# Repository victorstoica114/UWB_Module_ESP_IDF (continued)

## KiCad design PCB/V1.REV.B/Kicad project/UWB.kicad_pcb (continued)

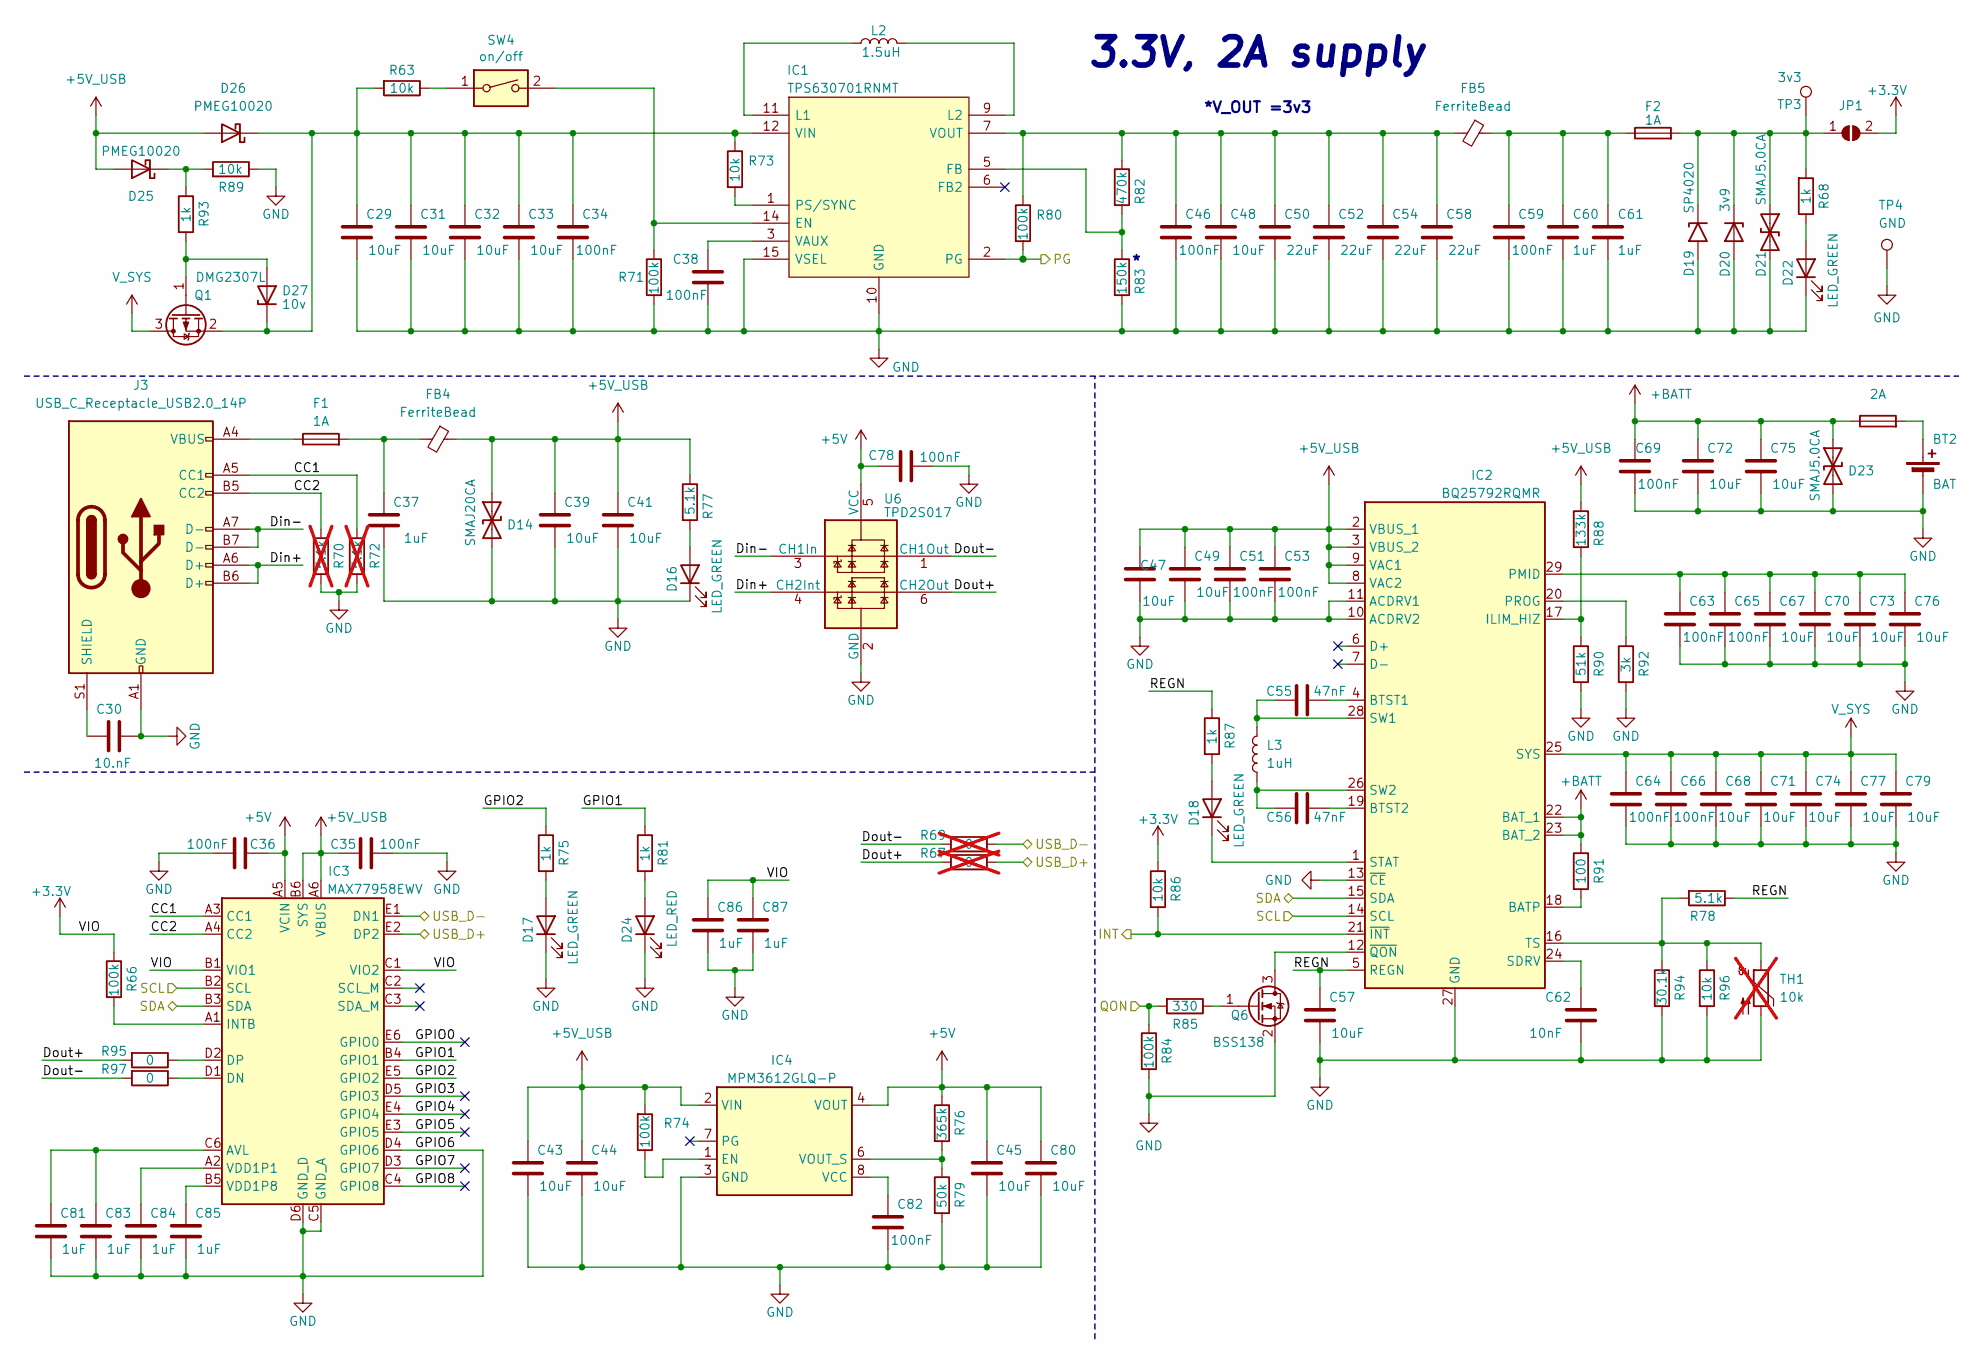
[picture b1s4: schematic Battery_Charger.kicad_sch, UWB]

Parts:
BT2: BAT; JST_PH_B2B-PH-K_1x02_P2.00mm_Vertical; Mfr. part number L475085; JLCPCB Part C131337
C29, C31, C32, C33, C39, C41, C43, C44, C45, C47, C48, C49, C57, C67, C68, C70, C71, C72, C73, C74, C75, C76, C77, C79, C80: 10uF; C_0603_1608Metric; Mfr. part number GRM188Z71A106KA73D; JLCPCB Part C19702
C30: 10.nF; C_1812_4532Metric; Mfr. part number CAS18C471JAGFC; JLCPCB Part C3287694
C34, C35, C36, C38, C46, C51, C53, C59, C63, C64, C65, C66, C69, C78, C82: 100nF; C_0603_1608Metric; Mfr. part number 06035C104KAZ4A; JLCPCB Part C14663
C37, C60, C61, C81, C83, C84, C85, C86, C87: 1uF; C_0603_1608Metric; Mfr. part number 885012206052; JLCPCB Part C15849
C50, C52, C54, C58: 22uF; C_1206_3216Metric; Mfr. part number CL31B226KPHNNNE; JLCPCB Part C12891
C55, C56: 47nF; C_0603_1608Metric; Mfr. part number 885012205054; JLCPCB Part C1622
C62: 10nF; C_0603_1608Metric; Mfr. part number SH18B103K160CT; JLCPCB Part C57112
D14: SMAJ20CA; D_SMA; Mfr. part number SMAJ20CA; JLCPCB Part C134970
D16, D17, D18, D22: LED_GREEN; LED_0603_1608Metric; Mfr. part number 150060VS75000; JLCPCB Part C22371297
D19: SP4020; D_SOD-323; Mfr. part number SP4020-01FTG-C; JLCPCB Part C126842
D20: 3v9; D_SMA; Mfr. part number BZG05C3V9-M3-08
D21, D23: SMAJ5.0CA; D_SMA; Mfr. part number SMAJ5.0CA; JLCPCB Part C83324
D24: LED_RED; LED_0603_1608Metric; Mfr. part number 150060RS75000; JLCPCB Part C965799
D25, D26: PMEG10020; D_SOD-123F; Mfr. part number PMEG10020ELR-QX; JLCPCB Part C8597
D27: 10v; D_SOD-123F; Mfr. part number 78-MMSZ4697-HE3_A-08; JLCPCB Part C2922775
F1, F2: 1A; Fuse_1206_3216Metric; Mfr. part number C1T 1; JLCPCB Part C2838907
F3: 2A; Fuse_1206_3216Metric; Mfr. part number C1T 2; JLCPCB Part C18211642
FB4, FB5: FerriteBead; L_0805_2012Metric; Mfr. part number BLM21SP601SN1D; JLCPCB Part C3716677
IC1: TPS630701RNMT; TPS630702RNMT; Mfr. part number TPS630702RNMR; JLCPCB Part C181473
IC2: BQ25792RQMR; Mfr. part number BQ25792RQMR; JLCPCB Part C2862876
IC3: MAX77958EWV; BGA30C50P6X5_307X262X69; Manufacturer_Part_Number MAX77958EWV
IC4: MPM3612GLQ-P; MPM3612GLQ33P; Mfr. part number MPM3612GLQ-P
J3: USB_C_Receptacle_USB2.0_14P; USB_C_Receptacle_GCT_USB4105-xx-A_16P_TopMnt_Horizontal; Mfr. part number USB4105-GF-A-120; JLCPCB Part C5184243
JP1: SolderJumper_2_Open; SolderJumper-2_P1.3mm_Open_RoundedPad1.0x1.5mm
L2: 1.5uH; L_Taiyo-Yuden_NR-60xx; Mfr. part number NRM6045T1R5NMRRV; JLCPCB Part C3221450
L3: 1uH; L_Taiyo-Yuden_NR-60xx; Mfr. part number NRS6045T1R0NMGKV; JLCPCB Part C1331878
Q1: DMG2307L; SOT-23; Mfr. part number DMG2307L-7; JLCPCB Part C102620
Q6: BSS138; SOT-23; Mfr. part number BSS138; JLCPCB Part C5224261
R63, R73, R86, R89, R96: 10k; R_0603_1608Metric; Mfr. part number CR0603-FX-1002ELF; JLCPCB Part C25804
R66, R71, R74, R80, R84: 100k; R_0603_1608Metric; Mfr. part number RC0603FR-10100KL; JLCPCB Part C25803
R67, R69: 0; R_0603_1608Metric; Mfr. part number RC0603FR-130RL; JLCPCB Part C21189; not fitted
R68, R75, R81, R87, R93: 1k; R_0603_1608Metric; Mfr. part number AC0603DR-071KL; JLCPCB Part C21190
R70, R72: 5.1k; R_0603_1608Metric; Mfr. part number AC0603FR-135K1L; JLCPCB Part C23186; not fitted
R76: 365k; R_0603_1608Metric; Mfr. part number RC0603FR-07365KL; JLCPCB Part C23031
R77, R78: 5.1k; R_0603_1608Metric; Mfr. part number AC0603FR-135K1L; JLCPCB Part C23186
R79: 50k; R_0603_1608Metric; Mfr. part number AC0603FR-0751KL; JLCPCB Part C861451
R82: 470k; R_0603_1608Metric; Mfr. part number AC0603FR-07470KL; JLCPCB Part C23178
R83: 150k; R_0603_1608Metric; Mfr. part number RC0603FR-13150KL; JLCPCB Part C22807
R85: 330; R_0603_1608Metric; Mfr. part number RE0603FRE07330RL; JLCPCB Part C23138
R88: 133k; R_0603_1608Metric; Mfr. part number RC0603FR-07133KL; JLCPCB Part C22870
R90: 51k; R_0603_1608Metric; Mfr. part number AC0603FR-0751KL; JLCPCB Part C18672
R91: 100; R_0603_1608Metric; Mfr. part number RE0603FRE07330RL; JLCPCB Part C22775
R92: 3k; R_0603_1608Metric; Mfr. part number 603-RC0603JR-073KL
R94: 30.1k; R_0603_1608Metric; Mfr. part number RC0603FR-0730K1L; JLCPCB Part C23000
R95, R97: 0; R_0603_1608Metric; Mfr. part number RC0603FR-130RL; JLCPCB Part C21189
SW4: on/off; SW_SPDT_PCM12; Mfr. part number PCM12SMTBR; JLCPCB Part C18197923
TH1: 10k; JST_PH_B2B-PH-K_1x02_P2.00mm_Vertical; Mfr. Part No. B2B-PH-K-S (LF)(SN); JLCPCB Part C25804; not fitted
TP3: 3v3; TestPoint_Pad_D2.0mm
TP4: GND; TestPoint_Pad_D2.0mm
U6: TPD2S017; SOT-23-6; Mfr. part number TPD2S017DBVR; JLCPCB Part C880115

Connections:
+3.3V: C86.1, C87.1, IC3.B1 (VIO1), IC3.C1 (VIO2), JP1.2 (B), R66.1, R86.1; also elsewhere on the board
+5V: C36.1, C45.1, C78.1, C80.1, IC3.A5 (VCIN), IC4.4 (VOUT), IC4.5 (VOUT_2), R76.1, U6.5 (VCC)
+5V_USB: C35.1, C39.1, C41.1, C43.1, C44.1, C47.1, C49.1, C51.1, C53.1, D14.1 (A1), D25.2 (A), D26.2 (A), FB4.1, IC2.2 (VBUS_1), IC2.3 (VBUS_2), IC2.8 (VAC2), IC2.9 (VAC1), IC2.31 (VAC1_2), IC3.A6 (VBUS), IC3.B6 (SYS), IC4.2 (VIN), R74.2, R77.1, R88.1
+BATT: C69.1, C72.1, C75.1, D23.1 (A1), F3.1, IC2.22 (BAT_1), IC2.23 (BAT_2), R91.1
/Battery_Charger and Power_Supply/CC1: IC3.A3 (CC1), J3.A5 (CC1), R72.1
/Battery_Charger and Power_Supply/CC2: IC3.A4 (CC2), J3.B5 (CC2), R70.1
/Battery_Charger and Power_Supply/Din+: J3.A6 (D+), J3.B6 (D+), U6.4 (CH2Int)
/Battery_Charger and Power_Supply/Din-: J3.A7 (D-), J3.B7 (D-), U6.3 (CH1In)
/Battery_Charger and Power_Supply/Dout+: R67.2, R95.2, U6.6 (CH2Out)
/Battery_Charger and Power_Supply/Dout-: R69.2, R97.2, U6.1 (CH1Out)
/Battery_Charger and Power_Supply/GPIO0: IC3.E6 (GPIO0)
/Battery_Charger and Power_Supply/GPIO1: IC3.B4 (GPIO1), R81.1
/Battery_Charger and Power_Supply/GPIO2: IC3.E5 (GPIO2), R75.1
/Battery_Charger and Power_Supply/GPIO3: IC3.D5 (GPIO3)
/Battery_Charger and Power_Supply/GPIO4: IC3.E4 (GPIO4)
/Battery_Charger and Power_Supply/GPIO5: IC3.E3 (GPIO5)
/Battery_Charger and Power_Supply/GPIO7: IC3.D3 (GPIO7)
/Battery_Charger and Power_Supply/GPIO8: IC3.C4 (GPIO8)
/Battery_Charger and Power_Supply/INT: IC2.21 (~INT), R86.2; also elsewhere on the board
/Battery_Charger and Power_Supply/PG: IC1.2 (PG), R80.2; also elsewhere on the board
/Battery_Charger and Power_Supply/QON: R84.1, R85.2; also elsewhere on the board
/Battery_Charger and Power_Supply/REGN: C57.1, IC2.5 (REGN), R78.1, R87.1
/Battery_Charger and Power_Supply/SCL: IC2.14 (SCL), IC3.B2 (SCL); also elsewhere on the board
/Battery_Charger and Power_Supply/SDA: IC2.15 (SDA), IC3.B3 (SDA); also elsewhere on the board
/Battery_Charger and Power_Supply/USB_D+: IC3.E2 (DP2), R67.1; also elsewhere on the board
/Battery_Charger and Power_Supply/USB_D-: IC3.E1 (DN1), R69.1; also elsewhere on the board
GND: BT2.2 (-), C29.2, C30.2, C31.2, C32.2, C33.2, C34.2, C35.2, C36.2, C37.2, C38.2, C39.2, C41.2, C43.2, C44.2, C45.2, C46.2, C47.2, C48.2, C49.2, C50.2, C51.2, C52.2, C53.2, C54.2, C57.2, C58.2, C59.2, C60.2, C61.2, C62.2, C63.2, C64.2, C65.2, C66.2, C67.2, C68.2, C69.2, C70.2, C71.2, C72.2, C73.2, C74.2, C75.2, C76.2, C77.2, C78.2, C79.2, C80.2, C81.2, C82.2, C83.2, C84.2, C85.2, C86.2, C87.2, D14.2 (A2), D16.1 (K), D17.1 (K), D19.2 (A2), D20.2 (A), D21.2 (A2), D22.1 (K), D23.2 (A2), D24.1 (K), IC1.4 (GND), IC1.10 (GND), IC1.15 (VSEL), IC2.10 (ACDRV2), IC2.11 (ACDRV1), IC2.13 (~CE), IC2.27 (GND), IC3.C5 (GND_A), IC3.D4 (GPIO6), IC3.D6 (GND_D), IC4.3 (GND), IC4.9 (GND_2), J3.A1 (GND), J3.A12 (GND), J3.B1 (GND), J3.B12 (GND), Q6.2 (S), R70.2, R71.2, R72.2, R79.2, R83.2, R84.2, R89.1, R90.2, R92.2, R94.2, R96.2, TH1.2, TP4.1, U6.2 (GND); also elsewhere on the board
unnamed: BT2.1 (+), F3.2
unnamed: C37.1, F1.2, FB4.2
unnamed: C59.1, C60.1, C61.1, F2.1, FB5.1
unnamed: D16.2 (A), R77.2
unnamed: D17.2 (A), R75.2
unnamed: D18.2 (A), R87.2
unnamed: D18.1 (K), IC2.1 (STAT), IC2.30 (STAT_2)
unnamed: D19.1 (A1), D20.1 (K), D21.1 (A1), F2.2, JP1.1 (A), R68.2, TP3.1
unnamed: D22.2 (A), R68.1
unnamed: D24.2 (A), R81.2
unnamed: D25.1 (K), R89.2, R93.1
unnamed: C29.1, C31.1, C32.1, C33.1, C34.1, D26.1 (K), D27.1 (K), IC1.12 (VIN), IC1.13 (VIN_2), IC1.A12 (VIN_3), Q1.2 (S), R63.2, R73.1
unnamed: D27.2 (A), Q1.1 (G), R93.2
unnamed: F1.1, J3.A4 (VBUS), J3.A9 (VBUS), J3.B4 (VBUS), J3.B9 (VBUS)
unnamed: IC1.14 (EN), R71.1, SW4.2
unnamed: IC1.5 (FB), R82.2, R83.1
unnamed: IC1.11 (L1), L2.2
unnamed: IC1.9 (L2), L2.1
unnamed: IC1.1 (PS/SYNC), R73.2
unnamed: C38.1, IC1.3 (VAUX)
unnamed: C46.1, C48.1, C50.1, C52.1, C54.1, C58.1, FB5.2, IC1.7 (VOUT), IC1.8 (VOUT_2), IC1.A7 (VOUT_3), R80.1, R82.1
unnamed: IC2.18 (BATP), R91.2
unnamed: C55.2, IC2.4 (BTST1)
unnamed: C56.2, IC2.19 (BTST2)
unnamed: IC2.17 (ILIM_HIZ), R88.2, R90.1
unnamed: C63.1, C65.1, C67.1, C70.1, C73.1, C76.1, IC2.29 (PMID)
unnamed: IC2.20 (PROG), R92.1
unnamed: C62.1, IC2.24 (SDRV), IC2.33 (SDRV_2)
unnamed: C55.1, IC2.28 (SW1), L3.2
unnamed: C56.1, IC2.26 (SW2), L3.1
unnamed: IC2.16 (TS), IC2.32 (TS_2), R78.2, R94.1, R96.1, TH1.1
unnamed: IC2.12 (~QON), Q6.3 (D)
unnamed: C81.1, C83.1, IC3.C6 (AVL)
unnamed: IC3.D1 (DN), R97.1
unnamed: IC3.D2 (DP), R95.1
unnamed: IC3.A1 (INTB), R66.2
unnamed: C84.1, IC3.A2 (VDD1P1)
unnamed: C85.1, IC3.B5 (VDD1P8)
unnamed: IC4.1 (EN), R74.1
unnamed: C82.1, IC4.8 (VCC)
unnamed: IC4.6 (VOUT_S), R76.2, R79.1
unnamed: C30.1, J3.S1 (SHIELD)
unnamed: Q6.1 (G), R85.1
unnamed: R63.1, SW4.1
V_SYS: C64.1, C66.1, C68.1, C71.1, C74.1, C77.1, C79.1, IC2.25 (SYS), Q1.3 (D)

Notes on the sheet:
3.3V, 2A supply
*V_OUT =3v3

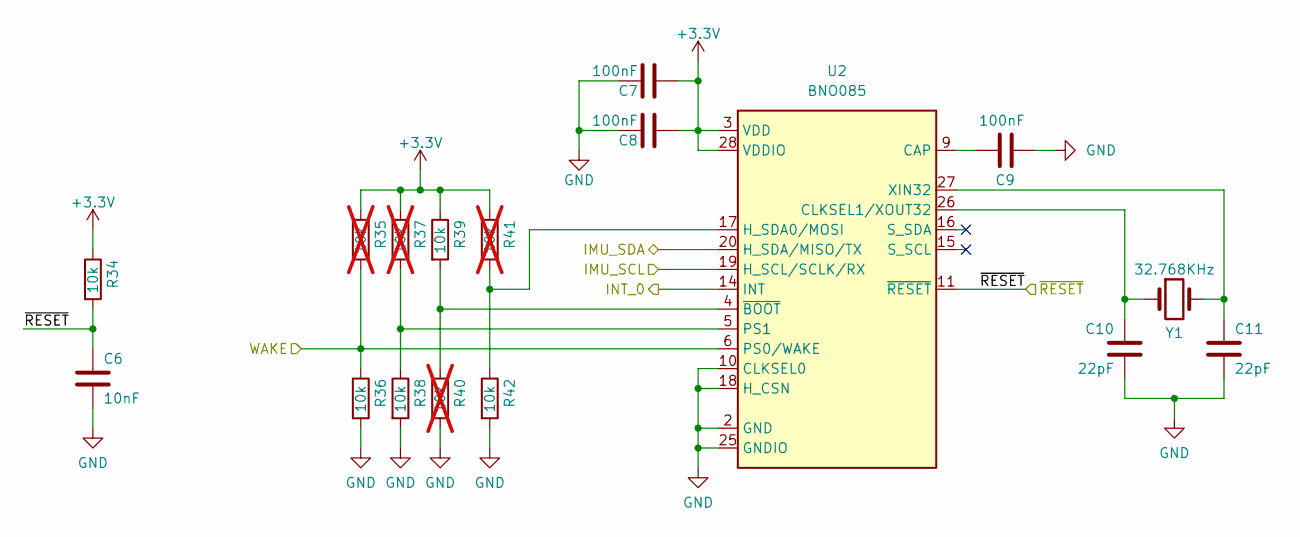
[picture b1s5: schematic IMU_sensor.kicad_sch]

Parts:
C6: 10nF; C_0603_1608Metric; Mfr. part number SH18B103K160CT; JLCPCB Part C57112
C7, C8, C9: 100nF; C_0603_1608Metric; Mfr. part number 06035C104KAZ4A; JLCPCB Part C14663
C10, C11: 22pF; C_0603_1608Metric; Mfr. part number 06033C220KAT2A; JLCPCB Part C1653
R34, R36, R38, R39, R42: 10k; R_0603_1608Metric; Mfr. part number CR0603-FX-1002ELF; JLCPCB Part C25804
R35, R37, R40, R41: 10k; R_0603_1608Metric; Mfr. part number CR0603-FX-1002ELF; JLCPCB Part C25804; not fitted
U2: BNO085; LGA-28_5.2x3.8mm_P0.5mm; Mfr. part number BNO085; JLCPCB Part C5189642
Y1: 32.768KHz; Crystal_SMD_2012-2Pin_2.0x1.2mm; Mfr. part number ABS06-32.768KHZ-T; JLCPCB Part C276423

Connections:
+3.3V: C7.2, C8.2, R34.1, R35.1, R37.1, R39.1, R41.1, U2.3 (VDD), U2.28 (VDDIO); also elsewhere on the board
/Battery_Charger and Power_Supply/SCL: U2.19 (H_SCL/SCLK/RX); also elsewhere on the board
/Battery_Charger and Power_Supply/SDA: U2.20 (H_SDA/MISO/TX); also elsewhere on the board
/ESP32/ESP32_IO14: R35.2, R36.1, U2.6 (PS0/WAKE); also elsewhere on the board
/ESP32/ESP32_IO15: U2.14 (INT); also elsewhere on the board
/IMU_sensor/~RESET: C6.1, R34.2, U2.11 (~RESET); also elsewhere on the board
GND: C6.2, C7.1, C8.1, C9.2, C10.2, C11.2, R36.2, R38.2, R40.2, R42.2, U2.2 (GND), U2.10 (CLKSEL0), U2.18 (H_CSN), U2.25 (GNDIO); also elsewhere on the board
unnamed: C9.1, U2.9 (CAP)
unnamed: C10.1, U2.26 (CLKSEL1/XOUT32), Y1.1
unnamed: R41.2, R42.1, U2.17 (H_SDA0/MOSI)
unnamed: R37.2, R38.1, U2.5 (PS1)
unnamed: C11.1, U2.27 (XIN32), Y1.2
unnamed: R39.2, R40.1, U2.4 (~BOOT)

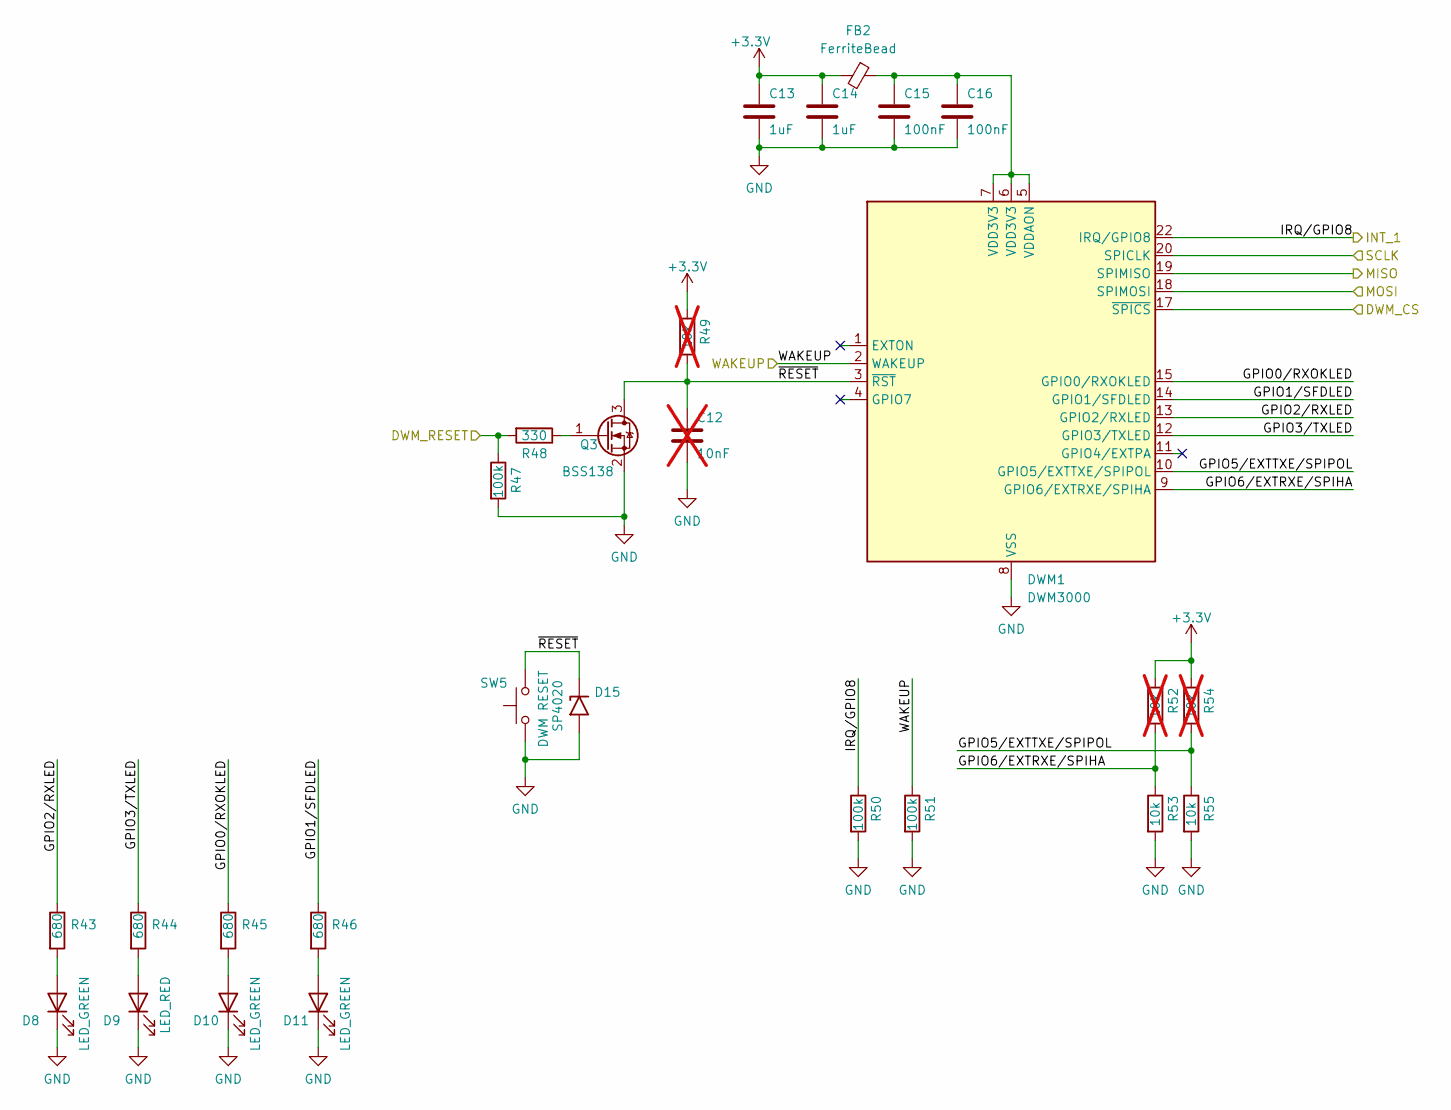
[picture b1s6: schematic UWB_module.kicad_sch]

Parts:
C12: 10nF; C_0603_1608Metric; Mfr. part number SH18B103K160CT; JLCPCB Part C57112; not fitted
C13, C14: 1uF; C_0603_1608Metric; Mfr. part number 885012206052; JLCPCB Part C15849
C15, C16: 100nF; C_0603_1608Metric; Mfr. part number 06035C104KAZ4A; JLCPCB Part C14663
D8, D10, D11: LED_GREEN; LED_0603_1608Metric; Mfr. part number 150060VS75000; JLCPCB Part C22371297
D9: LED_RED; LED_0603_1608Metric; Mfr. part number 150060RS75000; JLCPCB Part C965799
D15: SP4020; D_SOD-323; Mfr. part number SP4020-01FTG-C; JLCPCB Part C126842
DWM1: DWM3000; DWM1000; Mfr. part number DWM3000TR13; JLCPCB Part C5299931
FB2: FerriteBead; L_0805_2012Metric; Mfr. part number BLM21SP601SN1D; JLCPCB Part C3716677
Q3: BSS138; SOT-23; Mfr. part number BSS138; JLCPCB Part C5224261
R43, R44, R45, R46: 680; R_0603_1608Metric; Mfr. part number CRGCQ0603F680R; JLCPCB Part C23228
R47, R50, R51: 100k; R_0603_1608Metric; Mfr. part number RC0603FR-10100KL; JLCPCB Part C25803
R48: 330; R_0603_1608Metric; Mfr. part number RE0603FRE07330RL; JLCPCB Part C23138
R49, R52, R54: 10k; R_0603_1608Metric; Mfr. part number CR0603-FX-1002ELF; JLCPCB Part C25804; not fitted
R53, R55: 10k; R_0603_1608Metric; Mfr. part number CR0603-FX-1002ELF; JLCPCB Part C25804
SW5: DWM RESET; SW_Push_1P1T_NO_CK_KMR2; Mfr. part number PTS815SJM250SMTR LFS; JLCPCB Part C99271

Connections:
+3.3V: C13.1, C14.1, FB2.2, R49.1, R52.1, R54.1; also elsewhere on the board
/ESP32/ESP32_CS0: DWM1.17 (~SPICS); also elsewhere on the board
/ESP32/ESP32_IO8: R47.1, R48.2; also elsewhere on the board
/ESP32/ESP32_MISO: DWM1.19 (SPIMISO); also elsewhere on the board
/ESP32/ESP32_MOSI: DWM1.18 (SPIMOSI); also elsewhere on the board
/ESP32/ESP32_SCK: DWM1.20 (SPICLK); also elsewhere on the board
/UWB_module/GPIO0/RXOKLED: DWM1.15 (GPIO0/RXOKLED), R45.1
/UWB_module/GPIO1/SFDLED: DWM1.14 (GPIO1/SFDLED), R46.1
/UWB_module/GPIO2/RXLED: DWM1.13 (GPIO2/RXLED), R43.1
/UWB_module/GPIO3/TXLED: DWM1.12 (GPIO3/TXLED), R44.1
/UWB_module/GPIO5/EXTTXE/SPIPOL: DWM1.10 (GPIO5/EXTTXE/SPIPOL), R54.2, R55.1
/UWB_module/GPIO6/EXTRXE/SPIHA: DWM1.9 (GPIO6/EXTRXE/SPIHA), R52.2, R53.1
/UWB_module/IRQ/GPIO8: DWM1.22 (IRQ/GPIO8), R50.1; also elsewhere on the board
/UWB_module/WAKEUP: DWM1.2 (WAKEUP), R51.1; also elsewhere on the board
/UWB_module/~RESET: C12.1, D15.1 (A1), DWM1.3 (~RST), Q3.3 (D), R49.2, SW5.2
GND: C12.2, C13.2, C14.2, C15.2, C16.2, D8.1 (K), D9.1 (K), D10.1 (K), D11.1 (K), D15.2 (A2), DWM1.8 (VSS), DWM1.16 (VSS), DWM1.21 (VSS), DWM1.23 (VSS), DWM1.24 (VSS), Q3.2 (S), R47.2, R50.2, R51.2, R53.2, R55.2, SW5.1; also elsewhere on the board
unnamed: D8.2 (A), R43.2
unnamed: D9.2 (A), R44.2
unnamed: D10.2 (A), R45.2
unnamed: D11.2 (A), R46.2
unnamed: C15.1, C16.1, DWM1.5 (VDDAON), DWM1.6 (VDD3V3), DWM1.7 (VDD3V3), FB2.1
unnamed: Q3.1 (G), R48.1

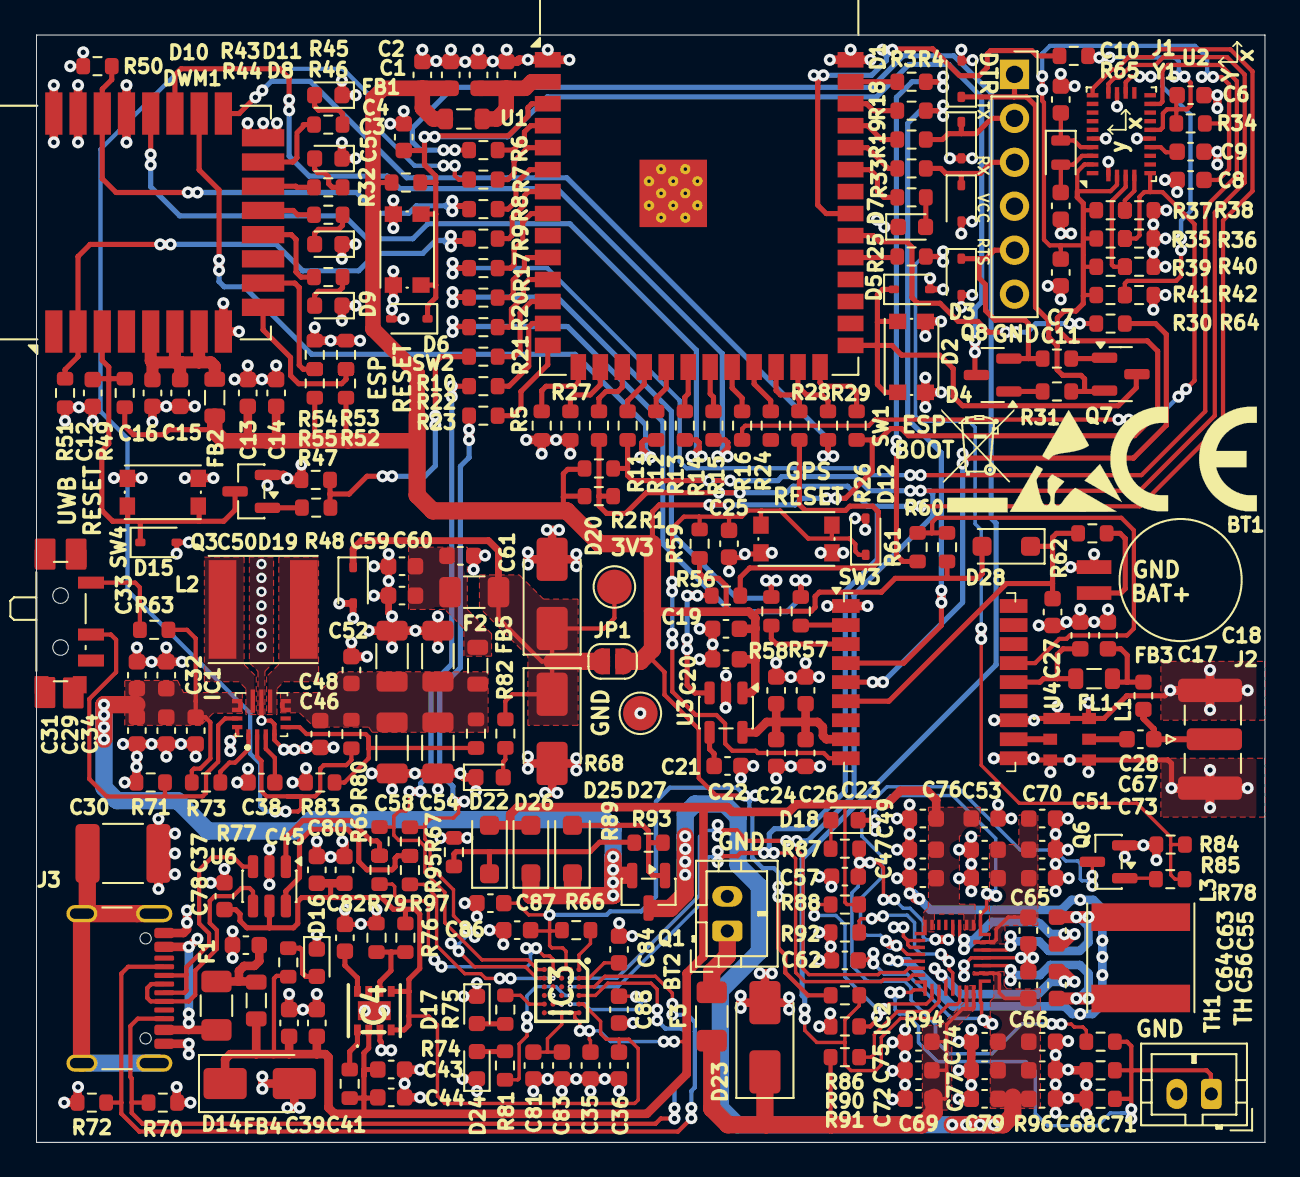
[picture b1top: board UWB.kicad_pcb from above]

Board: 4 copper layers, 71.0 x 64.0 mm, 254 parts (0 on the bottom side), 155 nets.

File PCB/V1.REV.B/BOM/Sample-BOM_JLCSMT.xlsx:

Comment | Designator | Footprint | JLCPCB Part #（optional）
Battery_1_Cell | BT2 | JST_PH_B2B-PH-K_1x02_P2.00mm_Vertical | C131337
22pF | C10 C11 | C_0603_1608Metric | C1653
47pF | C28 | C_0603_1608Metric | C23345
10nF | C6 C20 C21 C24 C62 | C_0603_1608Metric | C57112
47nF | C55 C56 | C_0603_1608Metric | C1622
100nF | C3 C4 C7 C8 C9 C15 C16 C17 C18 C23 C34 C38 C40 C42 C45 C46 C51 C53 C59 C63 C64 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 | C_0603_1608Metric | C14663
1uF | C1 C2 C5 C13 C14 C22 C25 C35 C36 C37 C43 C44 C60 C61 | C_0603_1608Metric | C15849
10uF | C19 C26 C29 C31 C32 C33 C39 C41 C47 C48 C49 C57 C67 C68 C70 C71 C72 C73 C74 C75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 | C_0603_1608Metric | C19702
22uF | C50 C52 C54 C58 | C_1206_3216Metric | C12891
3v6 | D20 D21 | D_SMA | C713621
LED_GREEN | D7 D8 D10 D11 D16 D18 D22 | LED_0603_1608Metric | C22371297
LED_RED | D9 D17 | LED_0603_1608Metric | C965799
SMAJ20CA | D14 D15 | D_SMA | C134970
SMAJ5.0CA | D23 | D_SMA | C83324
SP4020 | D1 D2 D3 D4 D5 D6 D12 D19 | D_SOD-323 | C126842
FerriteBead | FB1 FB2 FB3 FB4 FB5 | L_0805_2012Metric | C3716677
BQ25792RQMR | IC2 | BQ25792RQMR | C2862876
TPS630701RNMT | IC1 | TPS630702RNMT | C181473
27nH | L1 | L_0603_1608Metric | C98072
BSS138 | Q3 Q5 Q6 Q7 Q8 | SOT-23 | C5224261
DMP1046 | Q4 | DMP1046UFDB7 | C461048
0 | R22 R23 | R_0603_1608Metric | C21189
100 | R3 R4 R6 R7 R8 R9 R10 R11 R12 R13 R14 R15 R16 R17 R18 R19 R20 R21 R24 R25 R28 R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 | R_0603_1608Metric | C22775
330 | R48 R85 | R_0603_1608Metric | C23138
680 | R33 R43 R44 R45 R46 R95 | R_0603_1608Metric | C23228
1k | R56 R57 R58 R61 R66 R75 R76 R77 R78 R81 R87 | R_0603_1608Metric | C21190
3.01K | R92 | R_0603_1608Metric | C22991
5.1k | R64 R65 R79 | R_0603_1608Metric | C23186
5.23k | R93 | R_0603_1608Metric | C227977
10k | R1 R2 R5 R26 R27 R30 R31 R32 R34 R36 R38 R39 R42 R53 R55 R59 R60 R63 R67 R68 R6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 | R_0603_1608Metric | C25804
30.1k | R94 | R_0603_1608Metric | C137745
50k | R74 R90 | R_0603_1608Metric | C23196
100k | R47 R50 R51 R71 R80 R84 R88 R89 | R_0603_1608Metric | C25803
150k | R83 | R_0603_1608Metric | C22807
487k | R82 | R_0603_1608Metric | C13235
TPD2S017 | U6 | SOT-23-6 | C880115
32.768KHz | Y1 | Crystal_SMD_2012-2Pin_2.0x1.2mm | C276423
